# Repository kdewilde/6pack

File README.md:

# 6pack
KiCad files for 6pack macroPad

# Guide
1. Solder diodes
2. Solder reset button
3. clip reset button pins (interferes with switches)
4. Solder the pro micro header pins (do not solder the pro micro itself)
5. Solder the switches / rotary encoder
6. Clip switches under the pro micro (so it doesn't make contact)
7. Solder Pro Micro on with the components facing the PCB.
8. Add hotglue to the Pro Micro or make it hotswappable

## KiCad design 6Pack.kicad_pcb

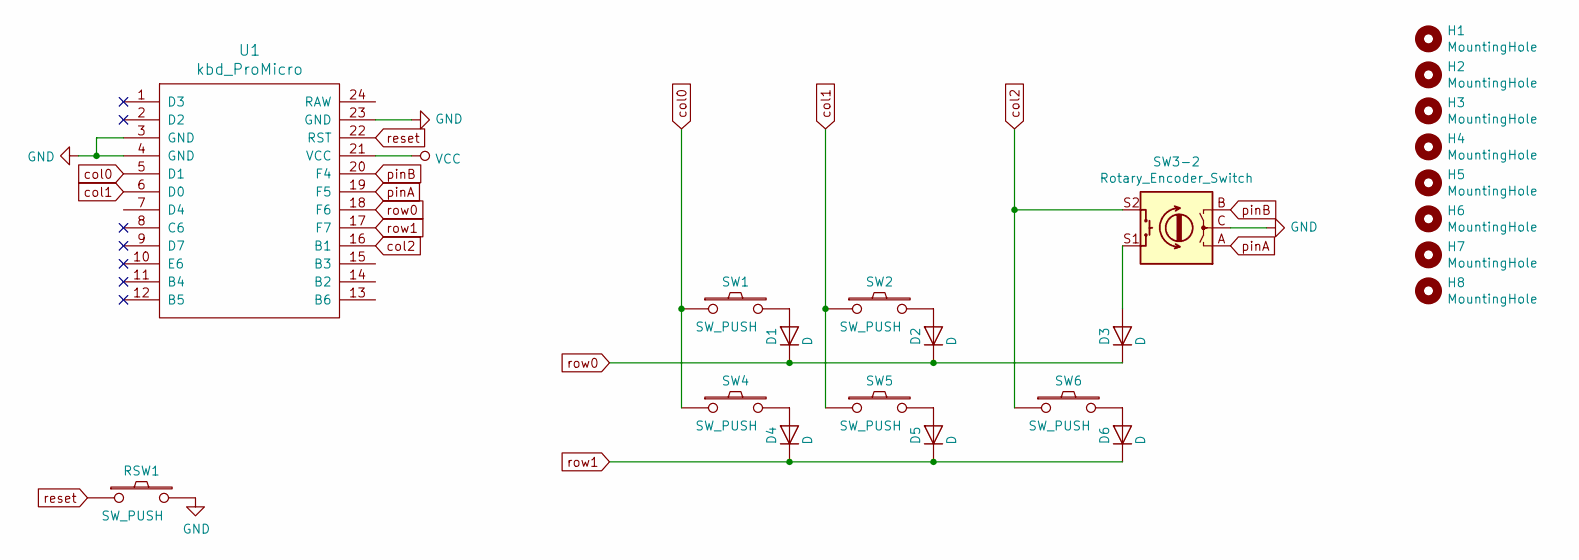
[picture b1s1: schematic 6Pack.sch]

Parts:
D1, D2, D3, D4, D5, D6: D; D_axial
H1, H2, H3, H4, H5, H6, H7, H8: MountingHole; MountingHole_2.2mm_M2
RSW1: SW_PUSH; SW_TACT_TH_HORIZ
SW1, SW2, SW4, SW5, SW6: SW_PUSH; MXOnly-1U
SW3-2: Rotary_Encoder_Switch; 1U-RotaryEncoder
U1: kbd_ProMicro; ArduinoProMicro

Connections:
GND: RSW1.2, SW3-2.C, U1.3 (GND), U1.4 (GND), U1.23 (GND)
unnamed: D1.2 (A), SW1.2
unnamed: D2.2 (A), SW2.2
unnamed: D3.2 (A), SW3-2.S1
unnamed: D4.2 (A), SW4.2
unnamed: D5.2 (A), SW5.2
unnamed: D6.2 (A), SW6.2
VCC: U1.21 (VCC)
col0: SW1.1, SW4.1, U1.5 (D1)
col1: SW2.1, SW5.1, U1.6 (D0)
col2: SW3-2.S2, SW6.1, U1.16 (B1)
pinA: SW3-2.A, U1.19 (F5)
pinB: SW3-2.B, U1.20 (F4)
reset: RSW1.1, U1.22 (RST)
row0: D1.1 (K), D2.1 (K), D3.1 (K), U1.18 (F6)
row1: D4.1 (K), D5.1 (K), D6.1 (K), U1.17 (F7)

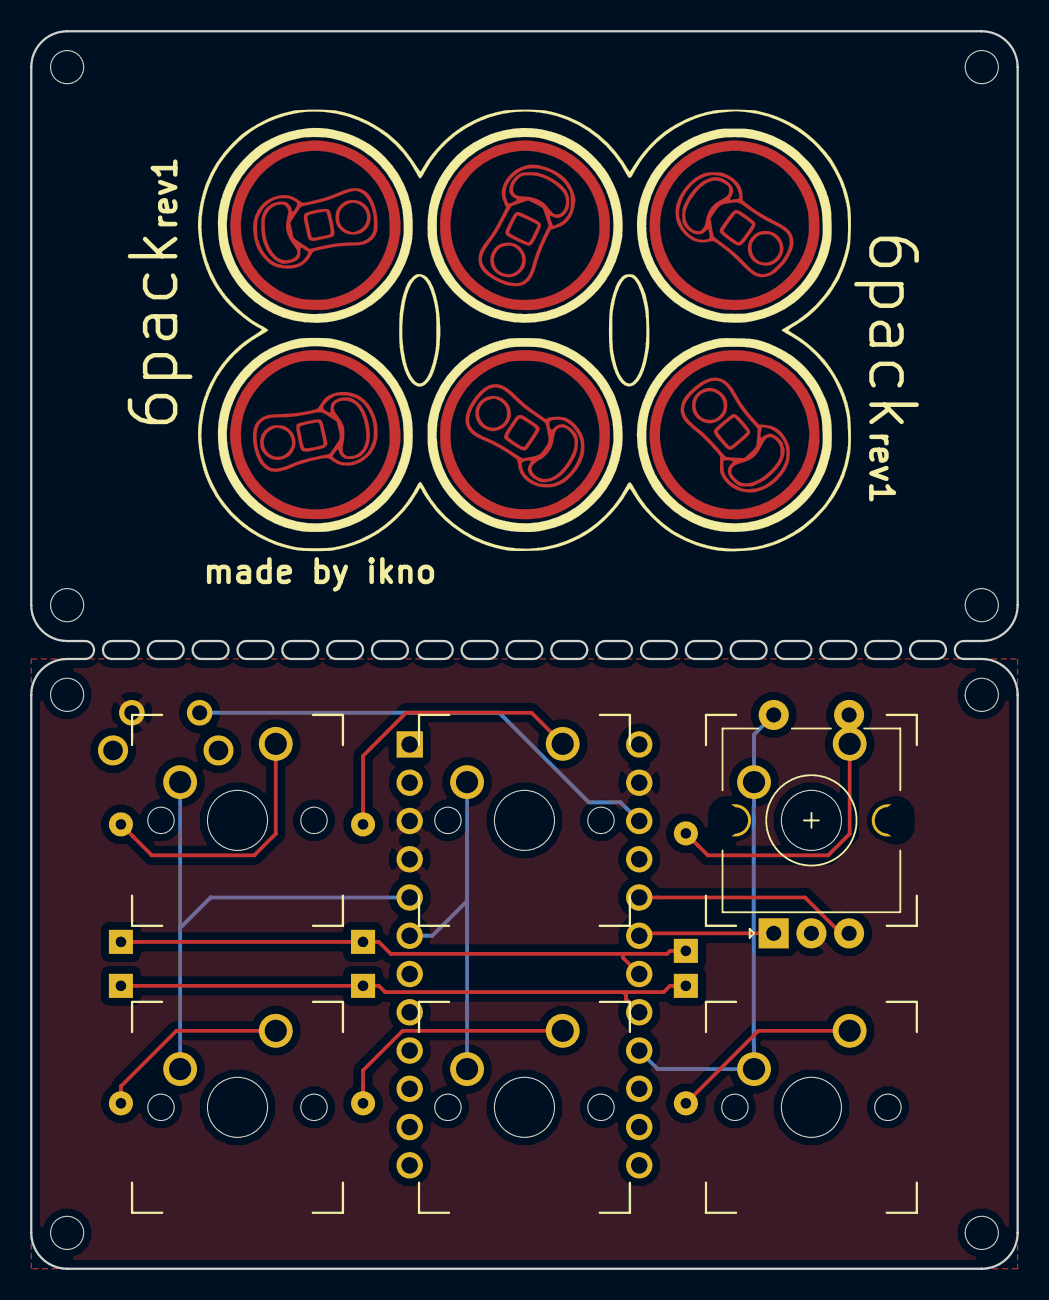
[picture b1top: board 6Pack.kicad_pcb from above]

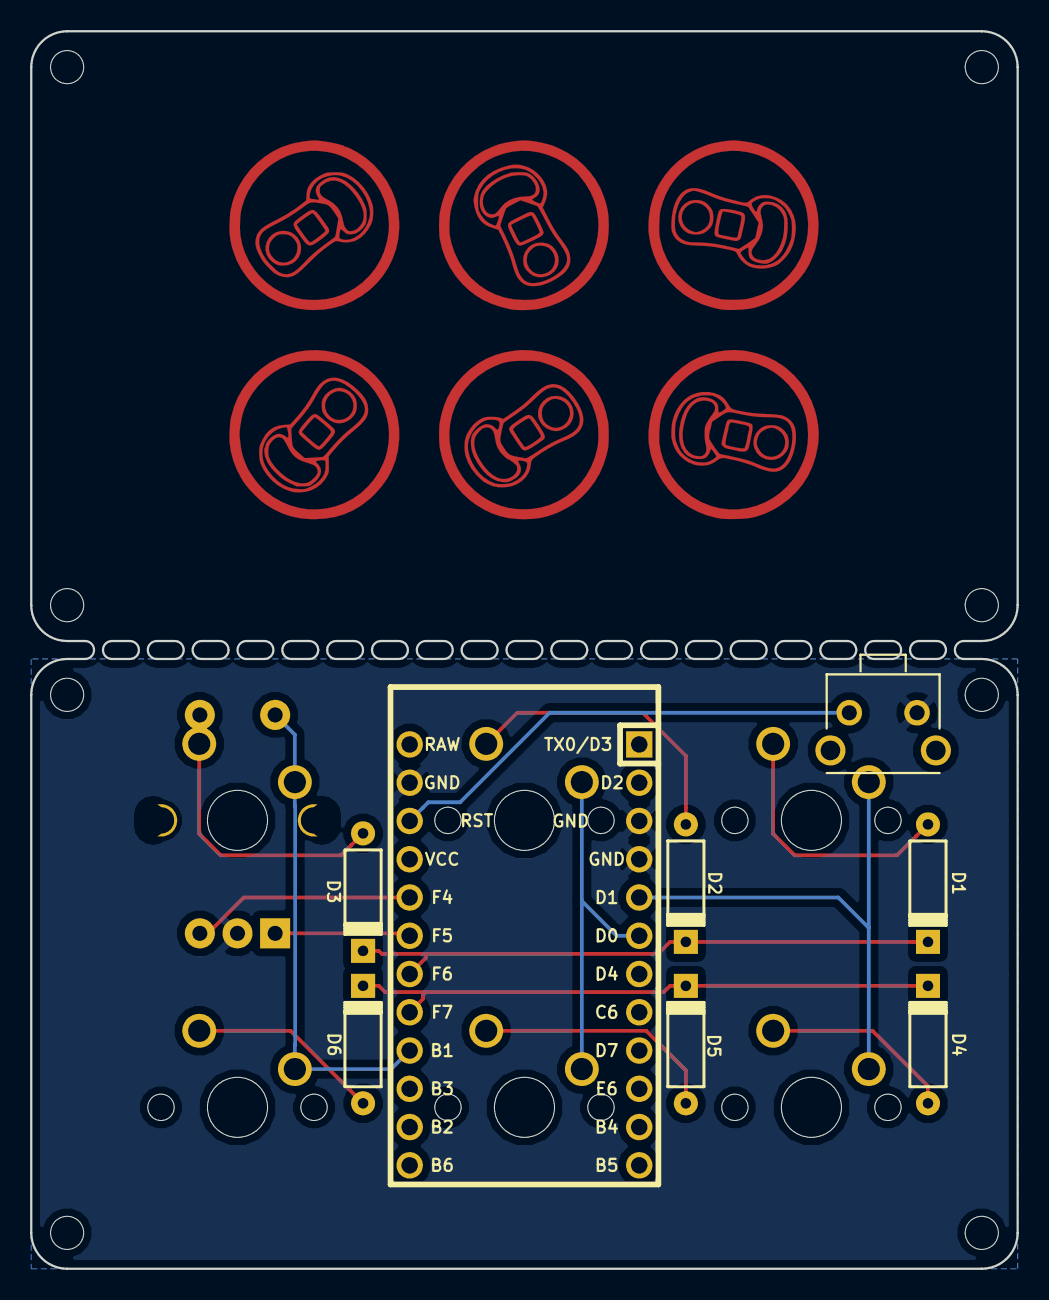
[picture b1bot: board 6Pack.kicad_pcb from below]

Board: 2 copper layers, 65.5 x 82.2 mm, 22 parts (7 on the bottom side), 15 nets.

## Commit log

2019-01-20 initial commit of the 6pack
